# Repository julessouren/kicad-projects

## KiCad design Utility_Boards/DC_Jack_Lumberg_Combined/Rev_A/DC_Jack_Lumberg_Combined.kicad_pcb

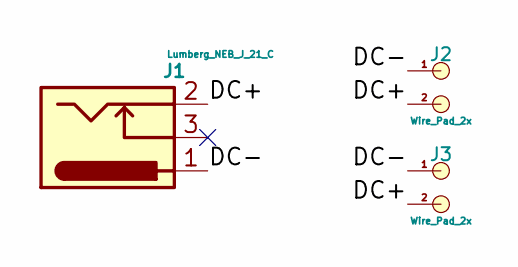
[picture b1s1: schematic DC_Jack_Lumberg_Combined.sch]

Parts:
J1: Lumberg_NEB_J_21_C; Lumberg_Combined_Bottom
J2, J3: Wire_Pad_2x; Wire_Pad_2x_1.0mm_Hole_1.5_Annular_2.54mm_Pitch

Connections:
/DC+: J1.2, J2.2, J3.2
/DC-: J1.1, J2.1, J3.1

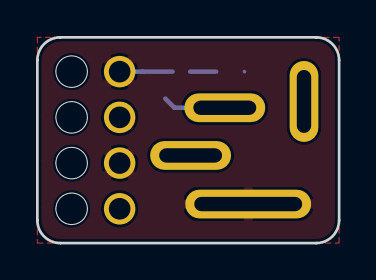
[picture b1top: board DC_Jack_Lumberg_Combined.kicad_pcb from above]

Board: 2 copper layers, 16.8 x 11.4 mm, 3 parts (0 on the bottom side), 2 nets.

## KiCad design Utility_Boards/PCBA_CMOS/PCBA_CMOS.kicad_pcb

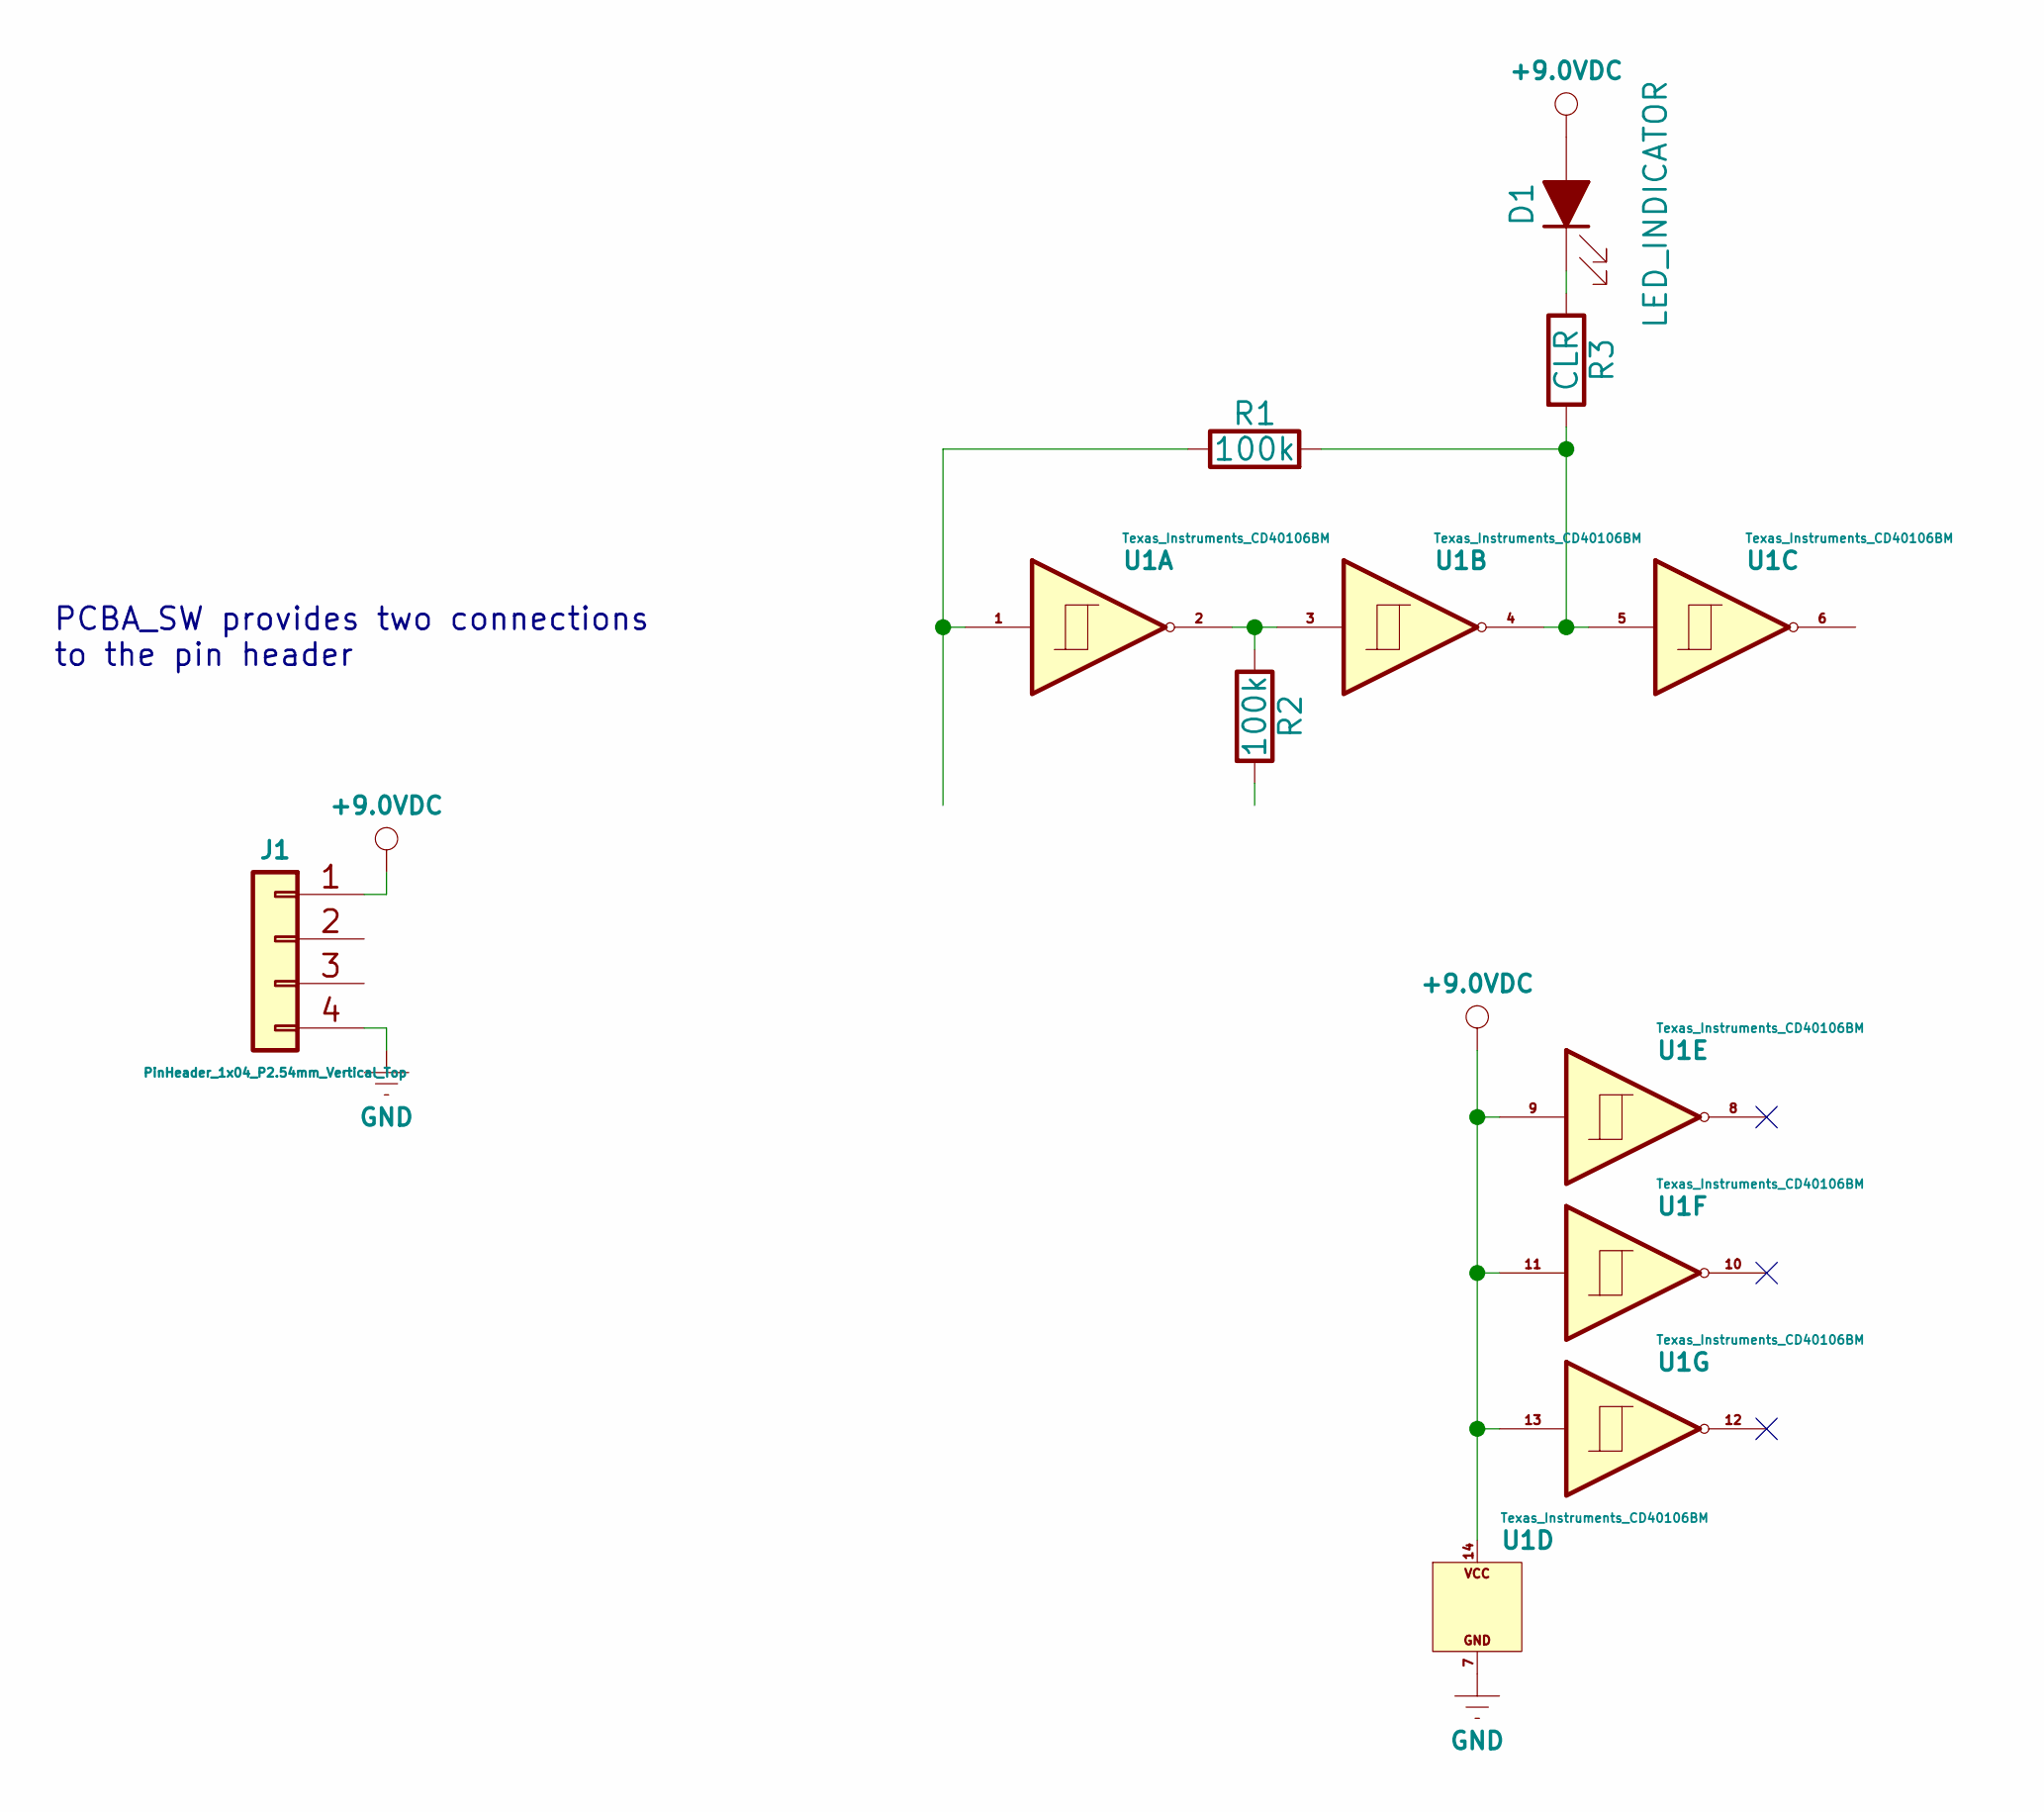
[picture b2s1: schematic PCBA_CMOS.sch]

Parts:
D1: LED_INDICATOR; Wire_Pad_2x_1.0mm_Hole_1.5_Annular
J1: PinHeader_1x04_P2.54mm_Vertical_Top
R1, R2: 100k; R_1206_3216M
R3: CLR; R_1206_3216M
U1: Texas_Instruments_CD40106BM; Texas_Instruments_CD40106BM_SOIC-14

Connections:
+9.0VDC: D1.2 (A), J1.1, U1.9, U1.11, U1.13, U1.14
GND: J1.4, U1.7
unnamed: D1.1 (K), R3.1
unnamed: R1.1, U1.1
unnamed: R1.2, R3.2, U1.4, U1.5
unnamed: R2.1, U1.2, U1.3

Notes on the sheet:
PCBA_SW provides two connections to the pin header

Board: 2 copper layers, 6 parts (3 on the bottom side), 6 nets, no tracks yet.

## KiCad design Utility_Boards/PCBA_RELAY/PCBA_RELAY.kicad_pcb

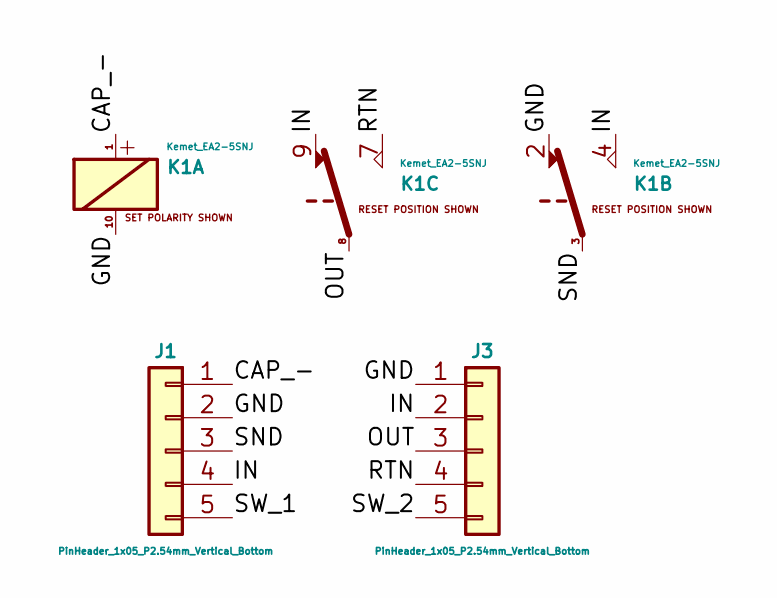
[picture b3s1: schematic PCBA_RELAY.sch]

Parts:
J1, J3: PinHeader_1x05_P2.54mm_Vertical_Bottom; PinHeader_1x05_P2.54mm_Vertical
K1: Kemet_EA2-5SNJ

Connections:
/CAP_-: J1.1, K1.1
/GND: J1.2, J3.1, K1.2, K1.10
/IN: J1.4, J3.2, K1.4, K1.9
/OUT: J3.3, K1.8
/RTN: J3.4, K1.7
/SND: J1.3, K1.3
/SW_1: J1.5
/SW_2: J3.5

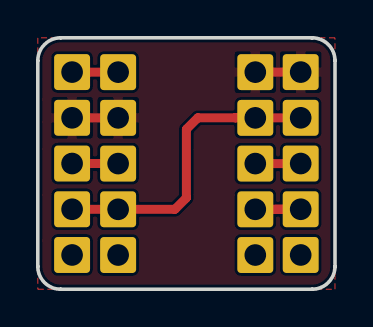
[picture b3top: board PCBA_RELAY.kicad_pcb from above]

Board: 2 copper layers, 16.5 x 14.0 mm, 3 parts (0 on the bottom side), 6 nets.

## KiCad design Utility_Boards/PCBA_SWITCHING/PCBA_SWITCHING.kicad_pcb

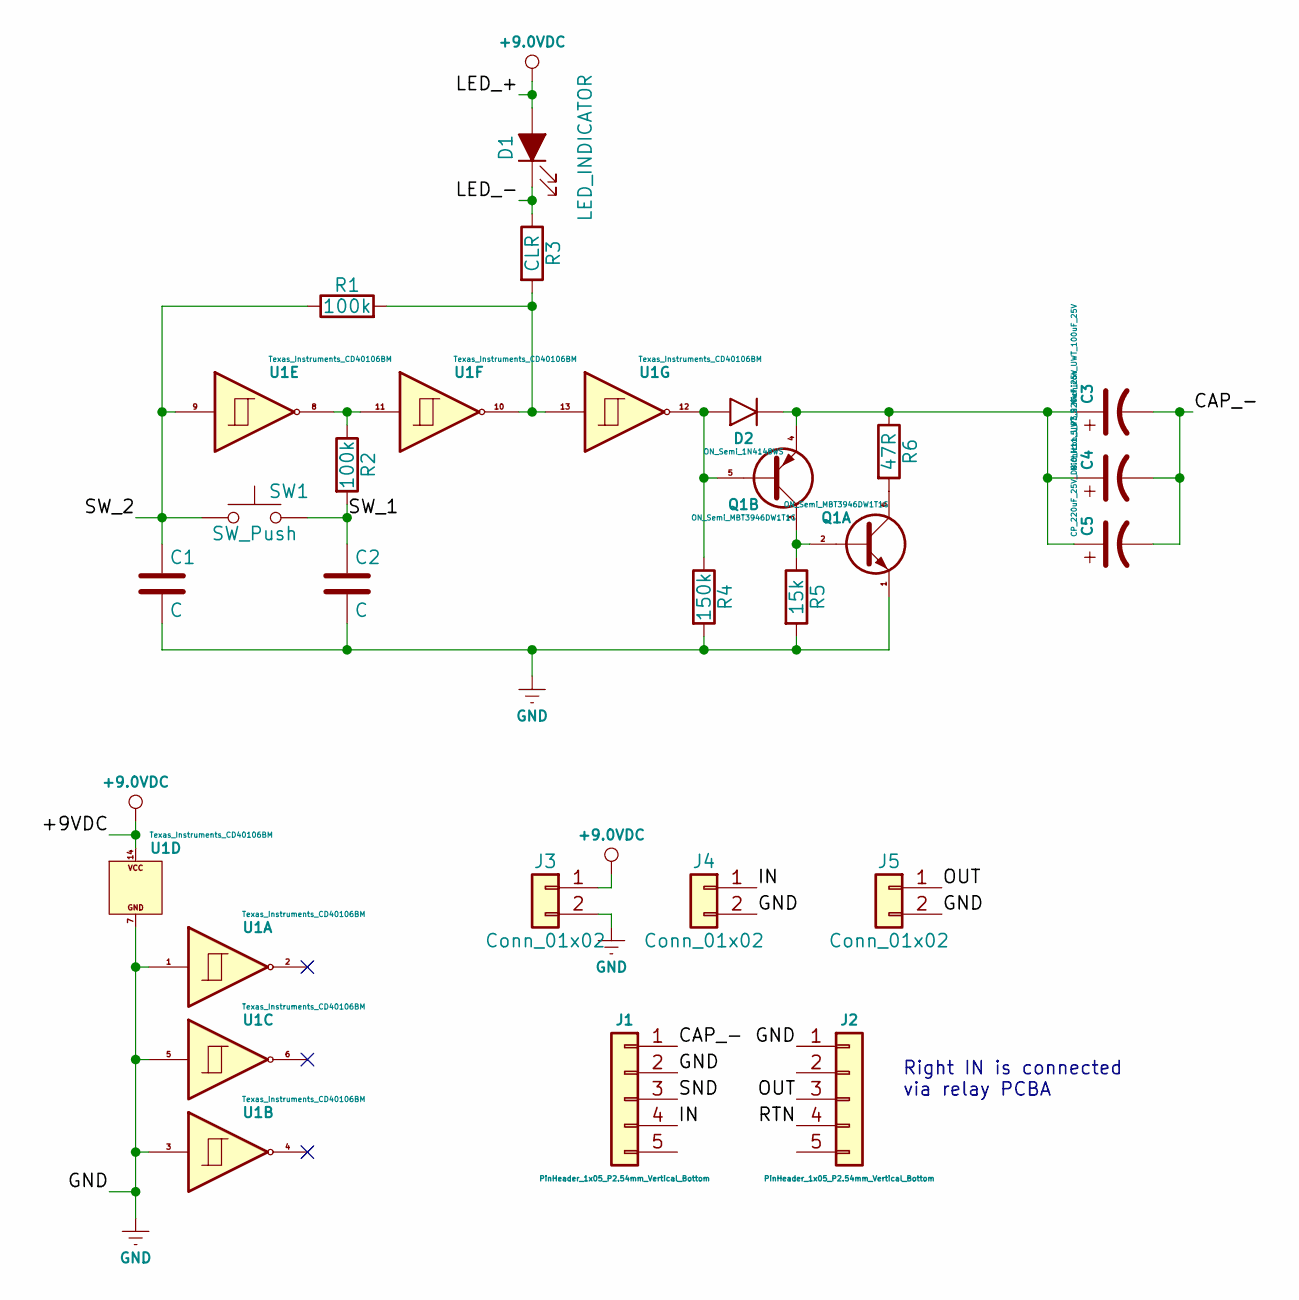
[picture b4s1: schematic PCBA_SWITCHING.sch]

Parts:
C1, C2: C; C_0603_1608M
C3: Nichicon_UWT_100uF_25V; Nichicon_UWT1E101MCL1GS_100uF_25V_6.3x7.7mm
C4: Nichicon_UWT_220uF_25V; Nichicon_UWT1E221MNL1GS_220uF_25V_8.0x10.0mm
C5: CP_220uF_25V_D8.0_H11.5_P3.5; Capacitor_Electrolytic_Radial_D8.0_H11.5_P3.5
D1: LED_INDICATOR; Wire_Pad_2x_1.0mm_Hole_1.5_Annular
D2: ON_Semi_1N4148WS; ON_Semi_1N4148WS_SOD-323F-2
J1, J2: PinHeader_1x05_P2.54mm_Vertical_Bottom; PinHeader_1x05_P2.54mm_Vertical
J3, J4, J5: Conn_01x02; Wire_Pad_2x_1.0mm_Hole_1.5_Annular_2.54mm_Pitch
Q1: ON_Semi_MBT3946DW1T1G; ON_Semi_MBT3946DW1T1G_SOT-363_SC-70-6_SC-80
R1, R2: 100k; R_0603_1608M
R3: CLR; R_0603_1608M
R4: 150k; R_0603_1608M
R5: 15k; R_0603_1608M
R6: 47R; R_0603_1608M
SW1: SW_Push; Wire_Pad_2x_1.0mm_Hole_1.5_Annular_2.54mm_Pitch
U1: Texas_Instruments_CD40106BM; Texas_Instruments_CD40106BM_SOIC-14

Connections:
+9.0VDC: D1.2 (A), J3.1, U1.14
/CAP_-: C3.2, C4.2, C5.2, J1.1
/IN: J1.4, J4.1
/LED_-: D1.1 (K), R3.1
/OUT: J2.3, J5.1
/RTN: J2.4
/SND: J1.3
/SW_1: C2.1, R2.2, SW1.2
/SW_2: C1.1, R1.1, SW1.1, U1.9
GND: C1.2, C2.2, J1.2, J2.1, J3.2, J4.2, J5.2, Q1.1 (E1), R4.2, R5.2, U1.1, U1.3, U1.5, U1.7
unnamed: C3.1, C4.1, C5.1, D2.1 (K), Q1.4 (E2), R6.1
unnamed: D2.2 (A), Q1.5 (B2), R4.1, U1.12
unnamed: Q1.2 (B1), Q1.3 (C2), R5.1
unnamed: Q1.6 (C1), R6.2
unnamed: R1.2, R3.2, U1.10, U1.13
unnamed: R2.1, U1.8, U1.11

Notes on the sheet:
Right IN is connected via relay PCBA

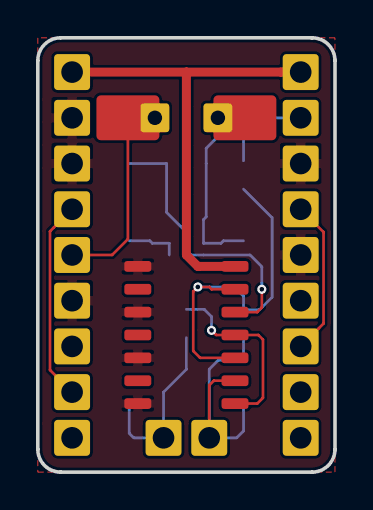
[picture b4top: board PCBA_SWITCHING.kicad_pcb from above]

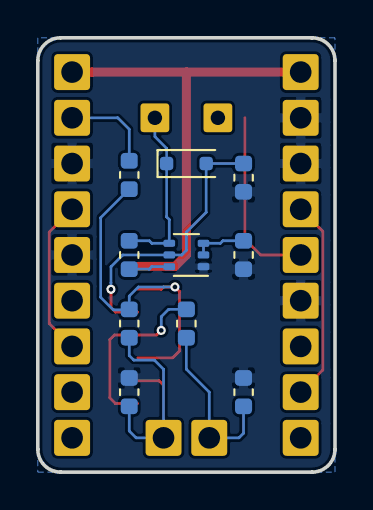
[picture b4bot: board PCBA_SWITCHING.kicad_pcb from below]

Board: 2 copper layers, 16.5 x 24.1 mm, 21 parts (10 on the bottom side), 14 nets.
